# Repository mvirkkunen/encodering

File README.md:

encodering (unfinished - the firmware for one has never even been run)
======================================================================

Yet another LED ring for encoders.

Features (once finished):

- LEDs in a ring (30 by default - but the LED layout is autogenerated)
- Handles encoder signals, presents simple counter register
- Multiple styles of ring display, automatically updated based on counter
- I2C based communication saving pins on your microcontroller
- Interrupt output pin
- Analog voltage output for simulated potentiometer

I2C protocol
------------

Write access:

- Write: [register] [data] [data...]

Read access:

- Write: [register]
- Read: [data] [data...]

Register pointer is auto-incremented.

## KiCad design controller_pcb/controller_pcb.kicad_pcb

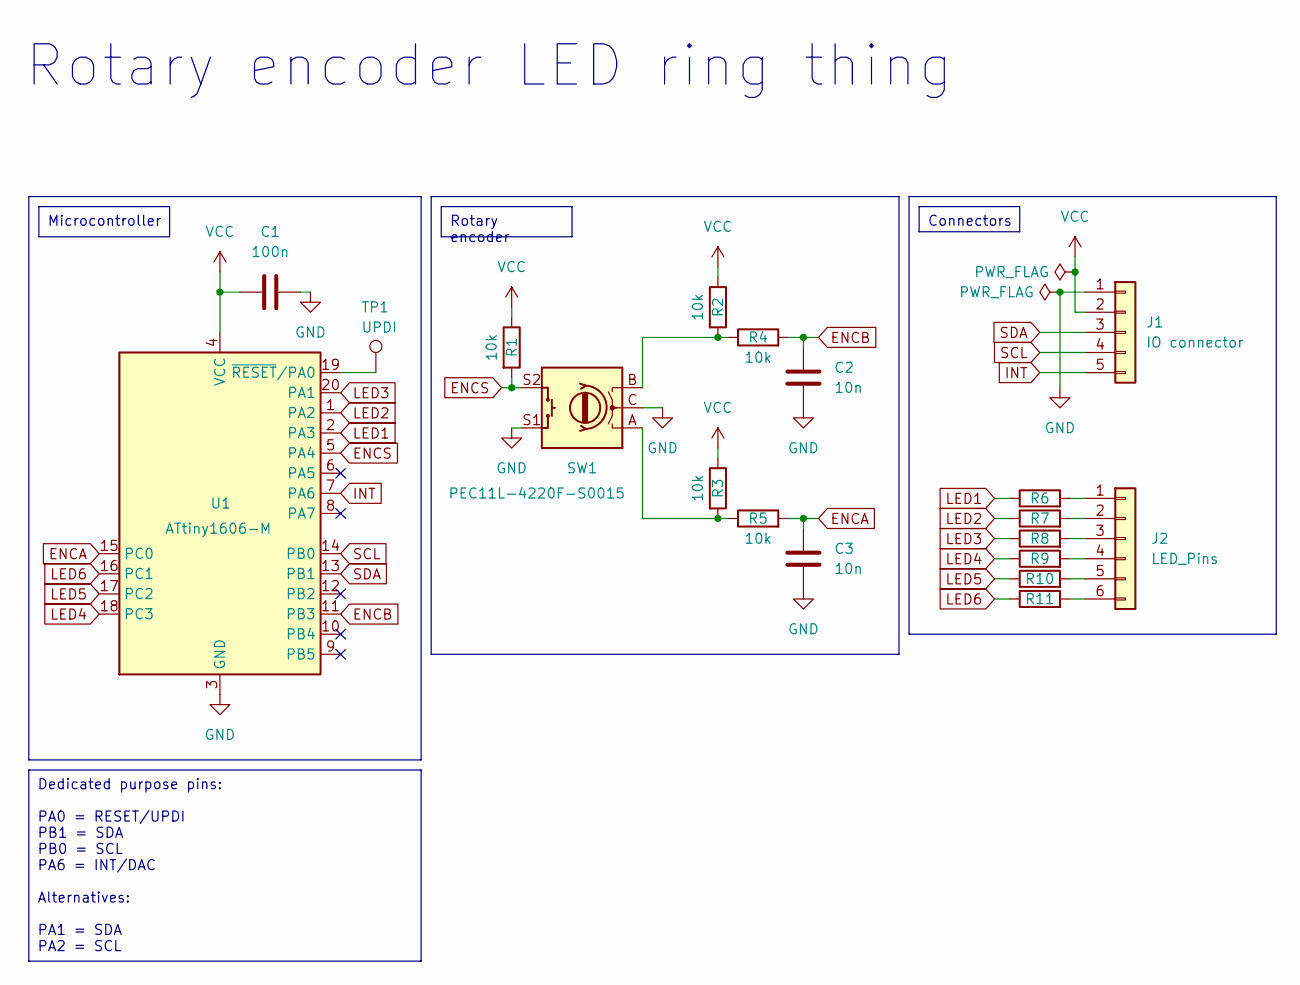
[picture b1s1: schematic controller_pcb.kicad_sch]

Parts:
C1: 100n; C_0603_1608Metric; LCSC C14663
C2, C3: 10n; C_0603_1608Metric; LCSC C57112
J1: IO connector; Project_PinHeader_1x05_P2.54mm_Vertical
J2: LED_Pins; Mounting_Hole_Pattern
R1, R2, R3, R4, R5: 10k; R_0603_1608Metric; LCSC C25804
R6, R7, R8, R9, R10, R11: 20ohm; R_0603_1608Metric; LCSC C22950
SW1: PEC11L-4220F-S0015; Project_RotaryEncoder_Bourns_Vertical_PEC12R-3x17F-Sxxxx
TP1: UPDI; TestPoint_Pad_D1.0mm
U1: ATtiny1606-M; Project_ATTINY1616_VQFN-20-1EP_3x3mm_P0.4mm_EP1.7x1.7mm; LCSC C507118

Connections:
ENCA: C3.2, R5.2, U1.15 (PC0)
ENCB: C2.2, R4.2, U1.11 (PB3)
ENCS: R1.2, SW1.S2, U1.5 (PA4)
GND: C1.2, C2.1, C3.1, J1.1, SW1.C, SW1.S1, U1.3 (GND), U1.21 (GND)
INT: J1.5, U1.7 (PA6)
LED1: R6.1, U1.2 (PA3)
LED2: R7.1, U1.1 (PA2)
LED3: R8.1, U1.20 (PA1)
LED4: R9.1, U1.18 (PC3)
LED5: R10.1, U1.17 (PC2)
LED6: R11.1, U1.16 (PC1)
unnamed: J2.1, R6.2
unnamed: J2.2, R7.2
unnamed: J2.3, R8.2
unnamed: J2.4, R9.2
unnamed: J2.5, R10.2
unnamed: J2.6, R11.2
unnamed: R2.2, R4.1, SW1.B
unnamed: R3.2, R5.1, SW1.A
unnamed: TP1.1, U1.19 (~RESET/PA0)
SCL: J1.4, U1.14 (PB0)
SDA: J1.3, U1.13 (PB1)
VCC: C1.1, J1.2, R1.1, R2.1, R3.1, U1.4 (VCC)

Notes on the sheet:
Microcontroller
Dedicated purpose pins: PA0 = RESET/UPDI PB1 = SDA PB0 = SCL PA6 = INT/DAC Alternatives: PA1 = SDA PA2 = SCL
Rotary encoder
Connectors
Rotary encoder LED ring thing

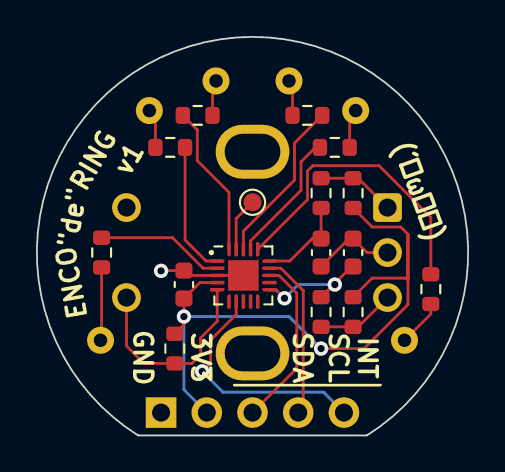
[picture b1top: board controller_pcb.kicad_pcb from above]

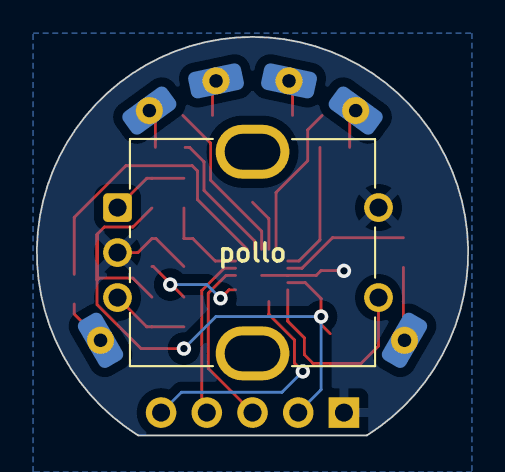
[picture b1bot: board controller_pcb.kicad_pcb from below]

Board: 2 copper layers, 24.0 x 22.1 mm, 19 parts (2 on the bottom side), 23 nets.

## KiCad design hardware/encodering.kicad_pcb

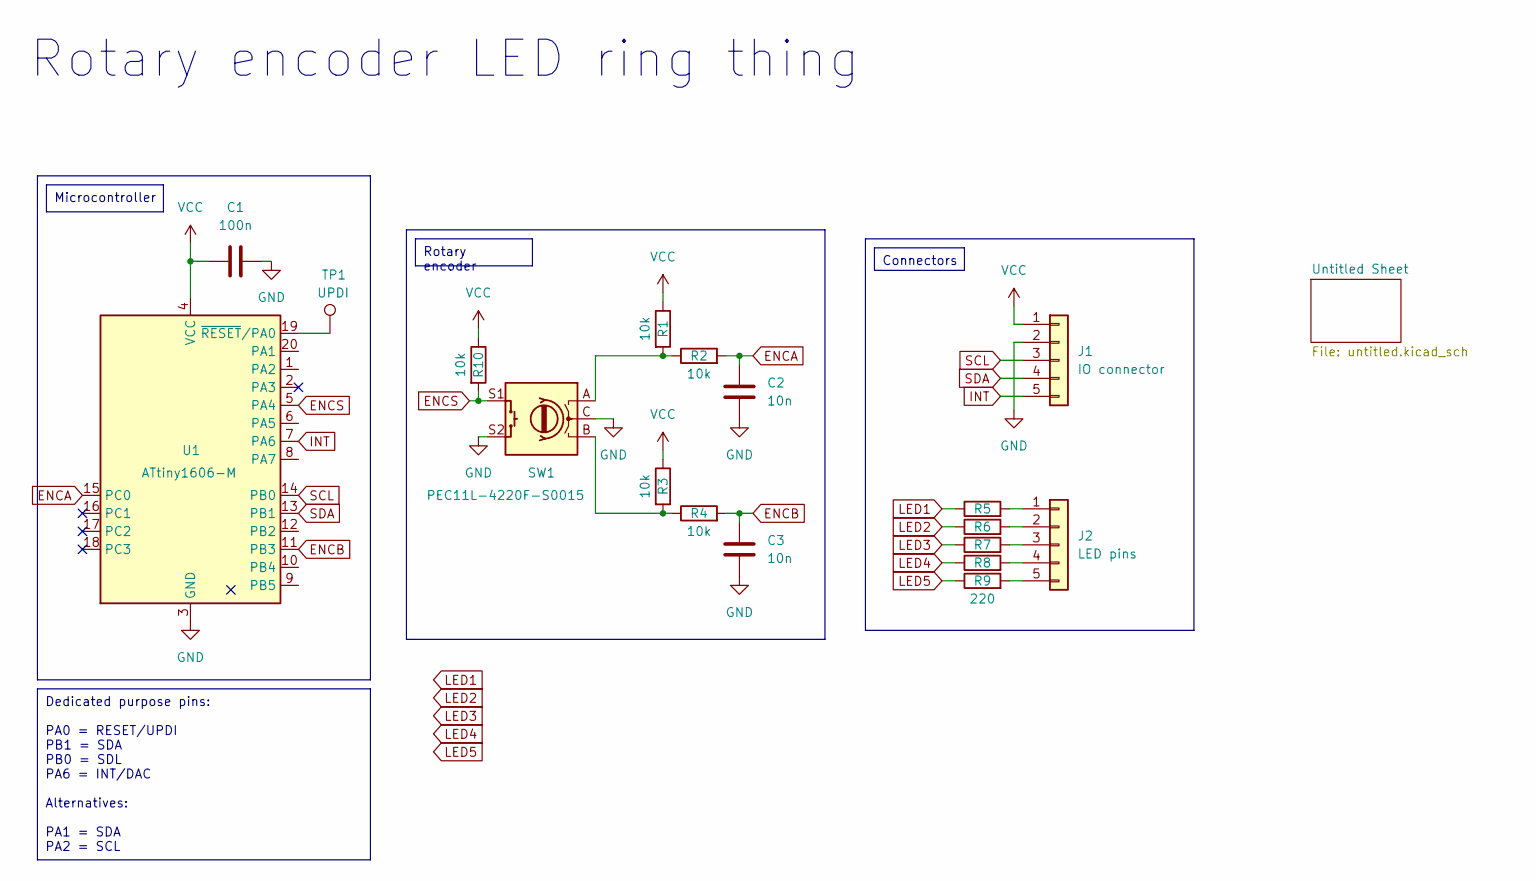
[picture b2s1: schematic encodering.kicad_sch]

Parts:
C1: 100n; C_0603_1608Metric
C2, C3: 10n; C_0603_1608Metric
J1: IO connector; PinHeader_1x05_P2.54mm_Vertical
J2: LED pins; PinHeader_1x05_P1.27mm_Vertical
R1, R2, R3, R4, R10: 10k; R_0603_1608Metric
R5, R6, R7, R8, R9: 220; R_0603_1608Metric
SW1: PEC11L-4220F-S0015; RotaryEncoder_Bourns_Vertical_PEC12R-3x17F-Sxxxx
TP1: UPDI; TestPoint_Pad_D1.5mm
U1: ATtiny1606-M; VQFN-20-1EP_3x3mm_P0.4mm_EP1.7x1.7mm

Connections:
ENCA: C2.2, R2.2, U1.15 (PC0)
ENCB: C3.2, R4.2, U1.11 (PB3)
ENCS: R10.2, SW1.S1, U1.5 (PA4)
GND: C1.2, C2.1, C3.1, J1.2, SW1.C, SW1.S2, U1.3 (GND), U1.21 (GND)
INT: J1.5, U1.7 (PA6)
LED1: R5.1
LED2: R6.1
LED3: R7.1
LED4: R8.1
LED5: R9.1
unnamed: J2.1, R5.2
unnamed: J2.2, R6.2
unnamed: J2.3, R7.2
unnamed: J2.4, R8.2
unnamed: J2.5, R9.2
unnamed: R1.2, R2.1, SW1.A
unnamed: R3.2, R4.1, SW1.B
unnamed: TP1.1, U1.19 (~RESET/PA0)
SCL: J1.3, U1.14 (PB0)
SDA: J1.4, U1.13 (PB1)
VCC: C1.1, J1.1, R1.1, R3.1, R10.1, U1.4 (VCC)

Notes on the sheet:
Microcontroller
Dedicated purpose pins: PA0 = RESET/UPDI PB1 = SDA PB0 = SDL PA6 = INT/DAC Alternatives: PA1 = SDA PA2 = SCL
Rotary encoder
Connectors
Rotary encoder LED ring thing

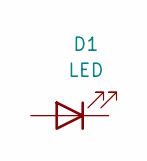
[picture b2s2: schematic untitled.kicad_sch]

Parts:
D1: LED; LED_0603_1608Metric

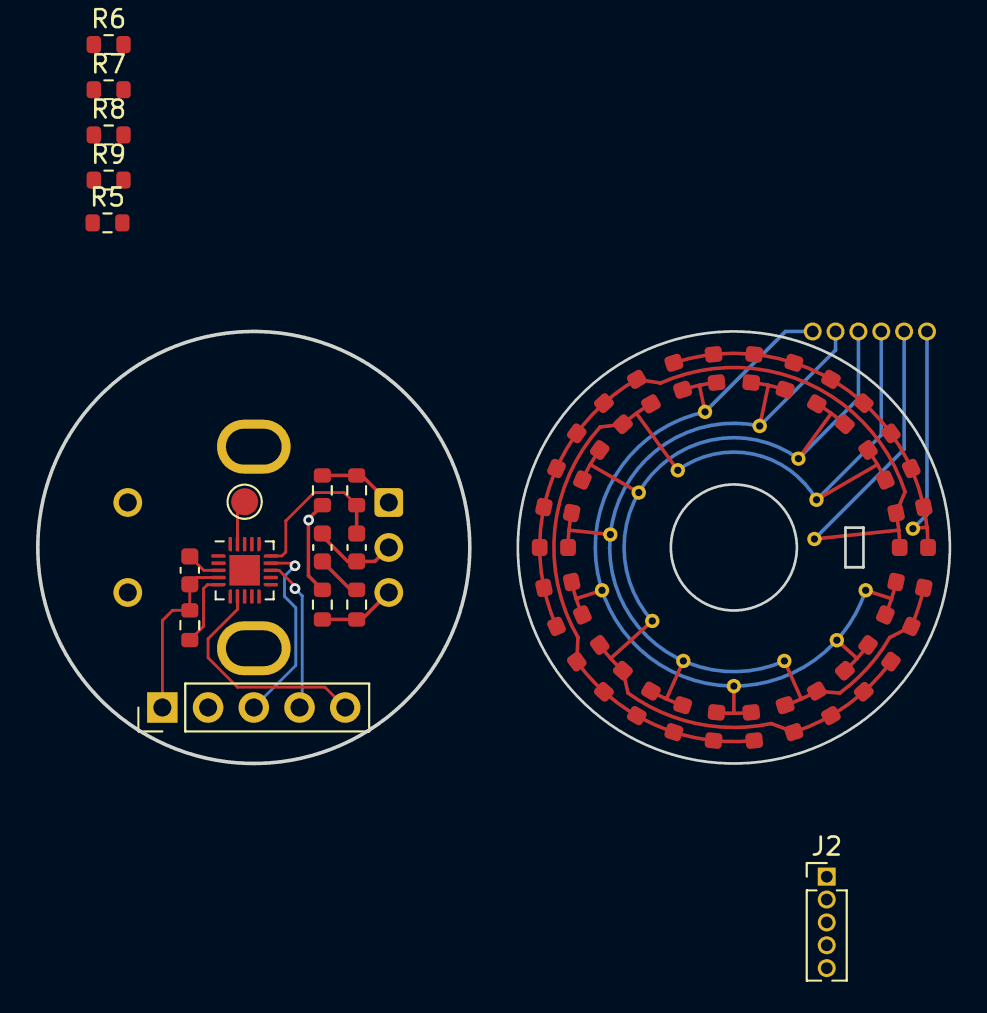
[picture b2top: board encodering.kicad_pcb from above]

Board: 2 copper layers, 50.7 x 24.0 mm, 18 parts (1 on the bottom side), 16 nets.

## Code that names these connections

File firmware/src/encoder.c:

#include <avr/interrupt.h>
#include <avr/io.h>
#include <stdbool.h>

#include "config.h"
#include "encoder.h"
#include "registers.h"
#include "unittest.h"

volatile int8_t encoder_delta = 0;

// ENCA = PC0
// ENCB = PB3
// ENCS = PA4

void encoder_init(void) {
    PORT_ENCA.PINCTRL_ENCA = PORT_ISC_BOTHEDGES_gc;
    PORT_ENCB.PINCTRL_ENCB = PORT_ISC_BOTHEDGES_gc;
}

void encoder_poll_button(void) {
    static bool prev_held = 0;

    bool held = PORT_ENCS.IN & BIT_ENCS;

    regs.status = (
        (held ? STATUS_BUTTON_HELD : 0)
        | ((held && !prev_held) ? STATUS_BUTTON_PRESSED : 0)
        | ((!held && prev_held) ? STATUS_BUTTON_RELEASED : 0)
    );
}

ISR(PORTA_PORT_vect) {
    uint8_t event = (
        0
        | !!(PORT_ENCA.IN & BIT_ENCA) << 3
        | !!(PORT_ENCB.IN & BIT_ENCB) << 2
        | !!(PORT_ENCA.INTFLAGS & BIT_ENCA) << 1
        | !!(PORT_ENCB.INTFLAGS & BIT_ENCB) << 0
    );

    switch (event) {
        case 0b1010:
        case 0b1101:
        case 0b0110:
        case 0b0001:
            encoder_delta++;
            break;
        case 0b0101:
        case 0b1110:
        case 0b1001:
        case 0b0010:
            encoder_delta--;
            break;
    }

    PORT_ENCB.INTFLAGS &= ~BIT_ENCB;
    PORT_ENCA.INTFLAGS &= ~BIT_ENCA;
}

ISR(PORTB_PORT_vect, ISR_ALIASOF(PORTA_PORT_vect));
ISR(PORTC_PORT_vect, ISR_ALIASOF(PORTA_PORT_vect));

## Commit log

2024-02-03 Kigen initial version
2024-02-03 Parsing support kinda
2024-02-03 More schematic parsing and serializing bits
2024-02-04 Attr fudging
2024-02-05 Kigen updates
2024-02-05 Refactoring
2024-02-05 Cleanup and docs
2024-02-05 Cleanup
2024-02-05 More typing stuff
2024-02-05 Initial hardware
2024-02-05 Initial firmware
2024-02-05 Get rid of to_sexpr duck typing
2024-02-05 Even more typing
2024-02-05 Fix more typing
2024-02-05 Make Pos2 not inherit Vec2
2024-02-05 Improve vecs, add Vec3
2024-02-05 Rename transform
2024-02-05 Regex based S-expression parser
2024-02-05 Use dict for metadata
2024-02-05 Improvements
2024-02-05 Hide things in modules for nicer intellisense
2024-02-05 Typing fixes
2024-02-05 Even more typing etc
2024-02-05 Started PCB stuff
2024-02-06 Optimize symbol parsing a bit
2024-02-06 Lotsa fixes
2024-02-10 LED ring generator 2.0 + kigen fixes
2024-02-10 Loadsa updates
2024-02-11 Model support
2024-02-11 Almost done
2024-02-11 More tweaks
2024-02-11 More fixes
2024-02-11 Cool bicolor LED support
2024-02-17 Kicadet links
2024-02-18 v1 for manufacturing
2024-02-18 ACTUAL manufactured version
2024-02-18 Color
2024-02-24 STEP stuff
2024-02-24 LED stuff
2024-02-24 HW stuff
2024-02-24 Lots firmware
2024-02-24 Implement encoder button, LED styles
2024-02-24 Fix some indexes
2024-02-24 Generate pin config
2024-02-24 Fix some types
2024-02-24 Enable more warnings
2024-02-24 Generate LED schedules outside of ISR
2024-02-24 Only updated schedule when changed
2024-02-24 Add simple unit testing framework
2024-02-25 Tests and fixes
2024-02-25 Improve io.h header handling in tests
2024-02-25 Remove outdated readme stuff
2024-02-25 Readme
2024-02-25 Script improvement
2024-02-25 Maybe a working encoder
2024-02-25 I2C tests
